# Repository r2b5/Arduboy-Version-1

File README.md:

# Arduboy-Version-1

This project is a derivative of the original **DIY Mini Retro Game Console** by MaDDy Regal (Uttar Pradesh, India), published on Instructables:  
https://www.instructables.com/DIY-Mini-Retro-Game-Console-With-Gmaes-Arduino-and/

## Hardware

- Arduino Nano  
- I2C Display 128x64 (SBC-OLED01 with SH1106 controller, Joy-IT)  
- Custom-designed PCB  

## Software

- Arduino IDE  
- Source code from the original project by MaDDy Regal  
- U8g2 graphics library: https://github.com/olikraus/u8g2  

## Project Goals

The main objective of this project is to teach apprentices and student interns the fundamentals of microcontroller programming. It also aims to provide a basic understanding of how such electronic systems function.

Additionally, the project serves as a foundation for progressing to more complex versions of retro gaming consoles and embedded systems.

## ToDo

- Implement sound functionality  
- Add battery support and charging circuit  

## Credits

- Original concept and source code by MaDDy Regal  
- U8g2 library by Oliver Kraus

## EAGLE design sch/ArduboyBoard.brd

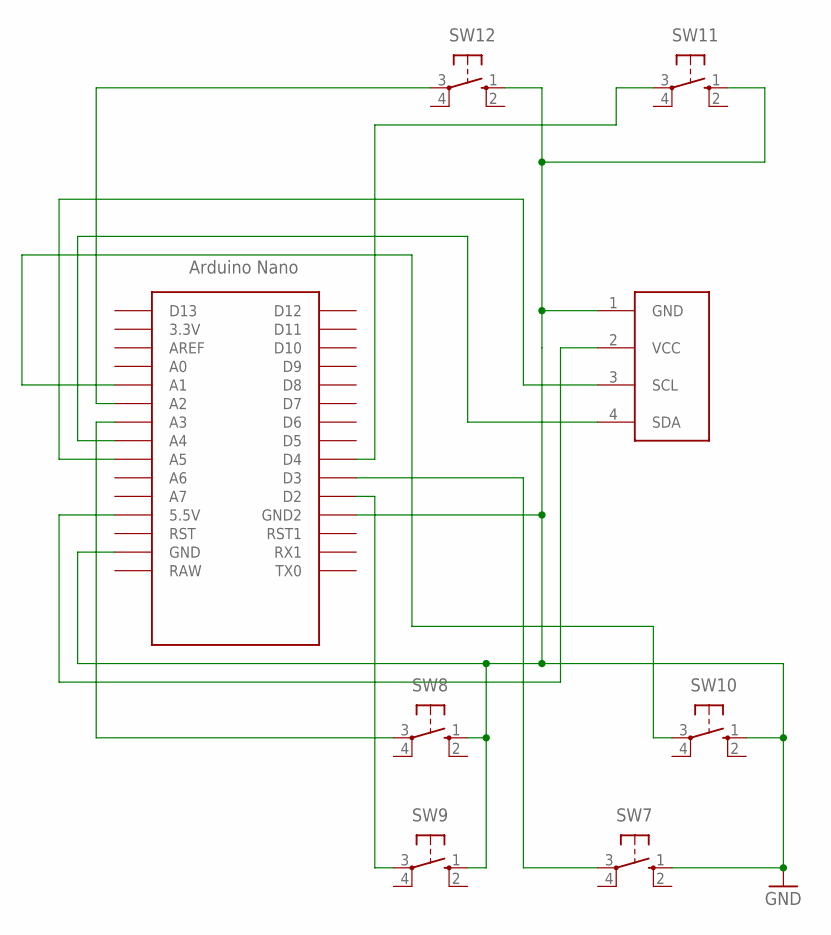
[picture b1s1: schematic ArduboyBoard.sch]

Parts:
SW7, SW8, SW9, SW10, SW11, SW12: 10-XX; B3F-10XX
U$1: NANO
U$2: I2C_OLED; I2C_OLED_PACKAGE

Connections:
GND: SW7.1 (S), SW8.1 (S), SW9.1 (S), SW10.1 (S), SW11.1 (S), SW12.1 (S), U$1.GND, U$1.GND1 (GND2), U$2.1 (GND)
unnamed: U$1.A5, U$2.3 (SCL)
unnamed: U$1.A4, U$2.4 (SDA)
unnamed: U$1.5V (5.5V), U$2.2 (VCC)
unnamed: SW8.3, U$1.A3
unnamed: SW12.3, U$1.A2
unnamed: SW10.3, U$1.A1
unnamed: SW9.3, U$1.D2
unnamed: SW7.3, U$1.D3
unnamed: SW11.3, U$1.D4

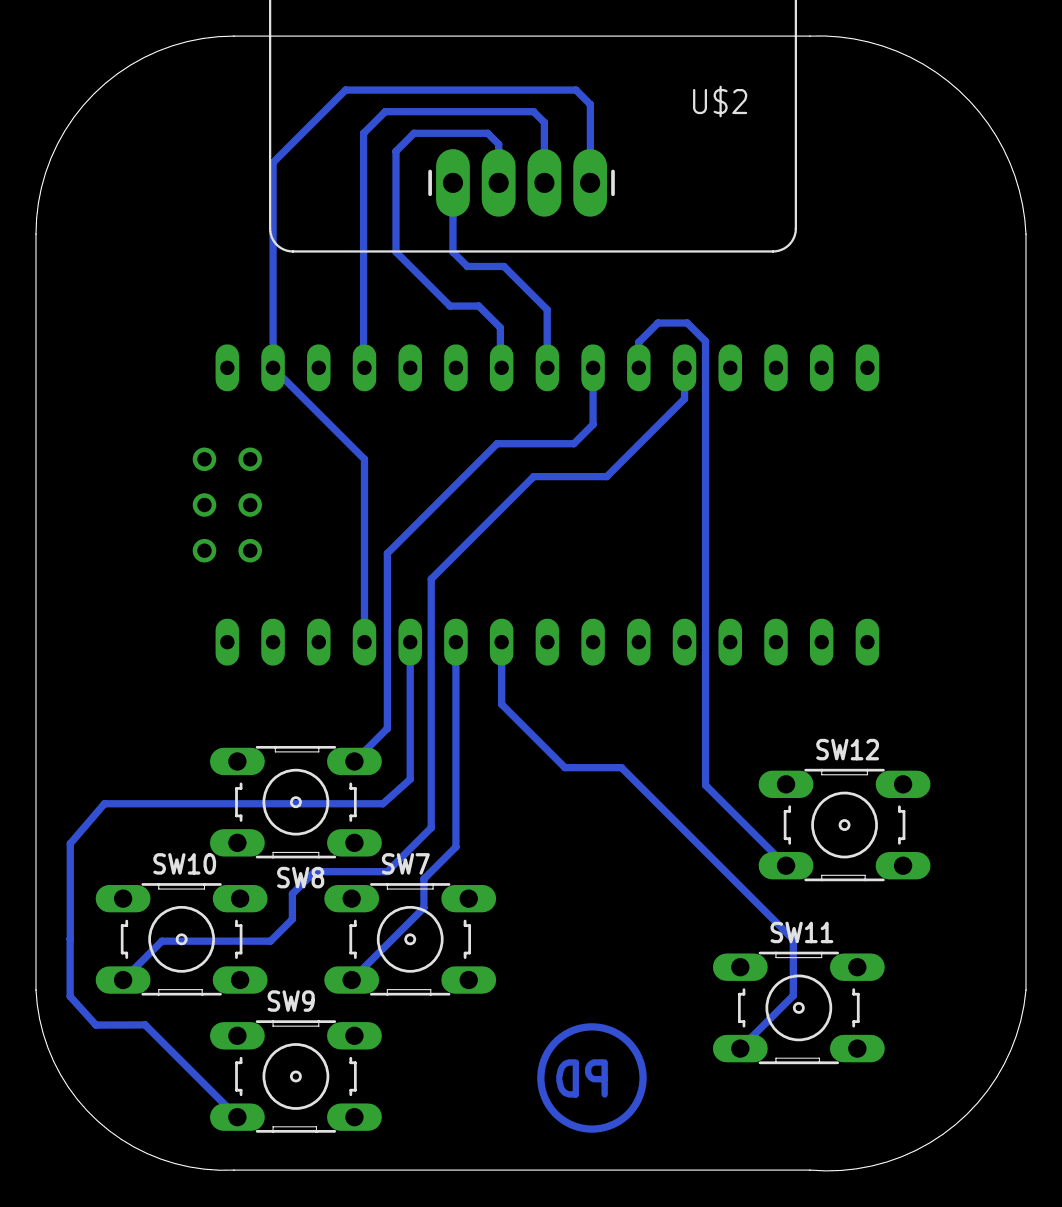
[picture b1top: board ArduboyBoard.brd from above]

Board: 2 copper layers, 55.0 x 63.0 mm, 8 parts (0 on the bottom side), 10 nets.

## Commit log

2026-03-18 Board PDFs
2026-03-18 Add image and attribution to README
    Added an image to the README and provided attribution.
2026-03-18 Simplify project description in README
    Clarified project goal in the README.
2026-03-18 Remove overview section from README
    Removed the overview section to streamline the README.
